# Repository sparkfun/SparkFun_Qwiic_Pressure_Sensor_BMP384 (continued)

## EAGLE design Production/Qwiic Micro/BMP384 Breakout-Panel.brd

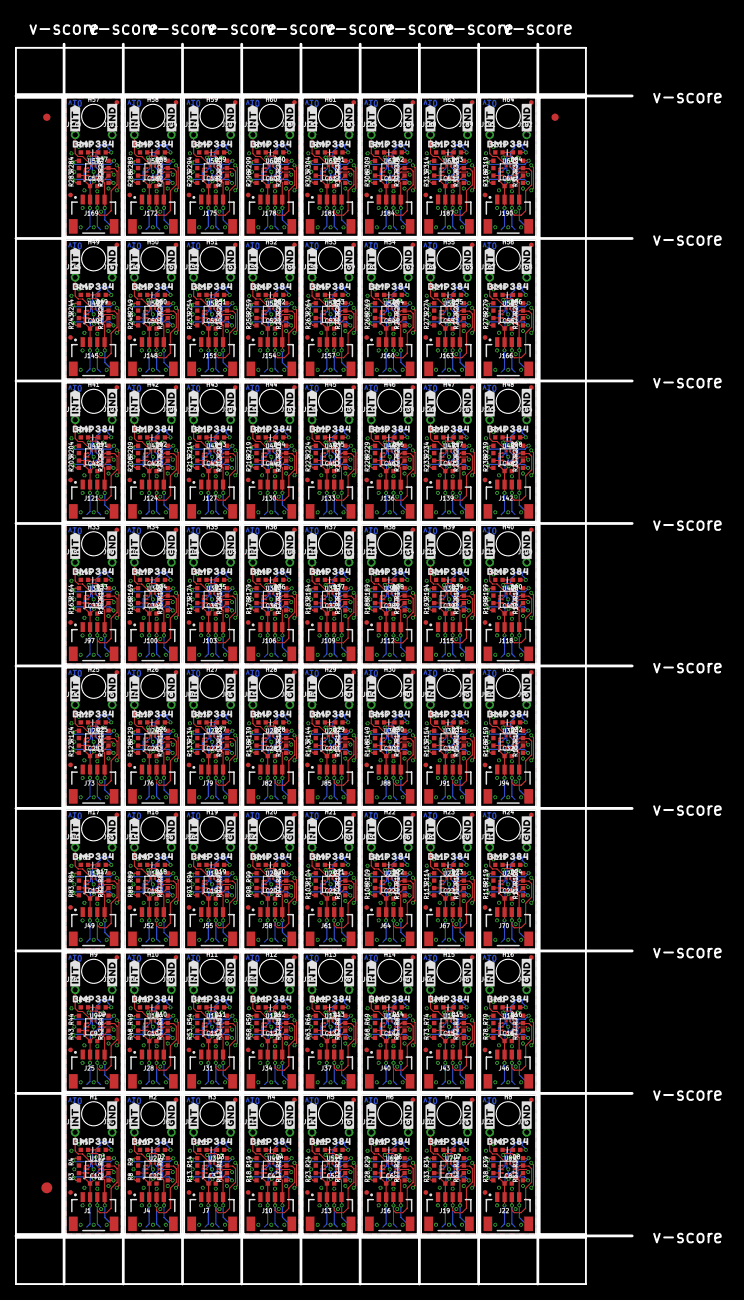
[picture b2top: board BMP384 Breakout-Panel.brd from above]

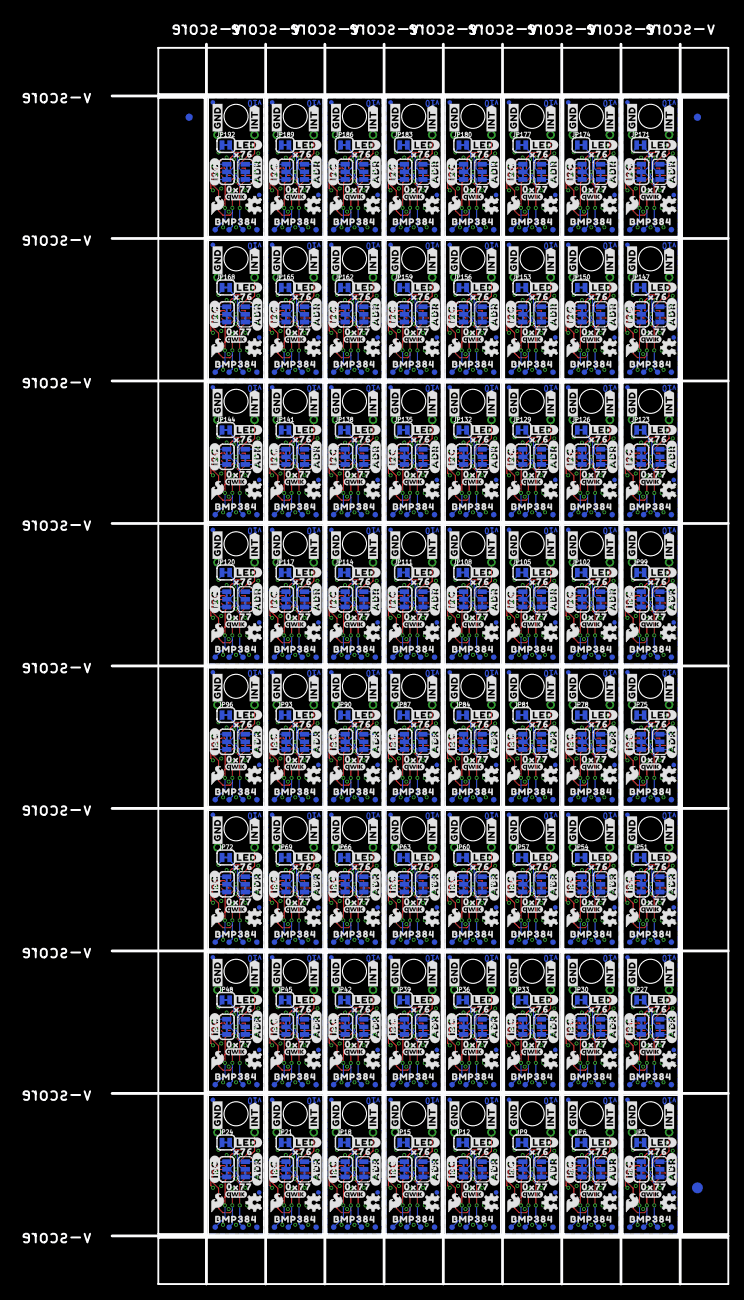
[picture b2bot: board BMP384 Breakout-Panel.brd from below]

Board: 4 copper layers, 84.6 x 170.2 mm, 2502 parts (1283 on the bottom side), 768 nets.

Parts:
C1, C2, C3, C4, C5, C6, C7, C8, C9, C10, C11, C12, C13, C14, C15, C16, C17, C18, C19, C20, C21, C22, C23, C24, C25, C26, C27, C28, C29, C30, C31, C32, C33, C34, C35, C36, C37, C38, C39, C40, C41, C42, C43, C44, C45, C46, C47, C48, C49, C50, C51, C52, C53, C54, C55, C56, C57, C58, C59, C60, C61, C62, C63, C64: 0.1uF; 0402-TIGHT
D1, D2, D3, D4, D5, D6, D7, D8, D9, D10, D11, D12, D13, D14, D15, D16, D17, D18, D19, D20, D21, D22, D23, D24, D25, D26, D27, D28, D29, D30, D31, D32, D33, D34, D35, D36, D37, D38, D39, D40, D41, D42, D43, D44, D45, D46, D47, D48, D49, D50, D51, D52, D53, D54, D55, D56, D57, D58, D59, D60, D61, D62, D63, D64: RED; LED-0402
E$1, E$2, E$3, E$4: FIDUCIAL-1X2
E$5, E$6: FIDUCIAL-1.5X3
FD1, FD2, FD3, FD4, FD5, FD6, FD7, FD8, FD9, FD10, FD11, FD12, FD13, FD14, FD15, FD16, FD17, FD18, FD19, FD20, FD21, FD22, FD23, FD24, FD25, FD26, FD27, FD28, FD29, FD30, FD31, FD32, FD33, FD34, FD35, FD36, FD37, FD38, FD39, FD40, FD41, FD42, FD43, FD44, FD45, FD46, FD47, FD48, FD49, FD50, FD51, FD52, FD53, FD54, FD55, FD56, FD57, FD58, FD59, FD60, FD61, FD62, FD63, FD64, FD65, FD66, FD67, FD68, FD69, FD70, FD71, FD72, FD73, FD74, FD75, FD76, FD77, FD78, FD79, FD80, FD81, FD82, FD83, FD84, FD85, FD86, FD87, FD88, FD89, FD90, FD91, FD92, FD93, FD94, FD95, FD96, FD97, FD98, FD99, FD100, FD101, FD102, FD103, FD104, FD105, FD106, FD107, FD108, FD109, FD110, FD111, FD112, FD113, FD114, FD115, FD116, FD117, FD118, FD119, FD120, FD121, FD122, FD123, FD124, FD125, FD126, FD127, FD128, FD129, FD130, FD131, FD132, FD133, FD134, FD135, FD136, FD137, FD138, FD139, FD140, FD141, FD142, FD143, FD144, FD145, FD146, FD147, FD148, FD149, FD150, FD151, FD152, FD153, FD154, FD155, FD156, FD157, FD158, FD159, FD160, FD161, FD162, FD163, FD164, FD165, FD166, FD167, FD168, FD169, FD170, FD171, FD172, FD173, FD174, FD175, FD176, FD177, FD178, FD179, FD180, FD181, FD182, FD183, FD184, FD185, FD186, FD187, FD188, FD189, FD190, FD191, FD192, FD193, FD194, FD195, FD196, FD197, FD198, FD199, FD200, FD201, FD202, FD203, FD204, FD205, FD206, FD207, FD208, FD209, FD210, FD211, FD212, FD213, FD214, FD215, FD216, FD217, FD218, FD219, FD220, FD221, FD222, FD223, FD224, FD225, FD226, FD227, FD228, FD229, FD230, FD231, FD232, FD233, FD234, FD235, FD236, FD237, FD238, FD239, FD240, FD241, FD242, FD243, FD244, FD245, FD246, FD247, FD248, FD249, FD250, FD251, FD252, FD253, FD254, FD255, FD256: FIDUCIALUFIDUCIAL; FIDUCIAL-MICRO
FRAME1, FRAME2, FRAME3, FRAME4, FRAME5, FRAME6, FRAME7, FRAME8, FRAME9, FRAME10, FRAME11, FRAME12, FRAME13, FRAME14, FRAME15, FRAME16, FRAME17, FRAME18, FRAME19, FRAME20, FRAME21, FRAME22, FRAME23, FRAME24, FRAME25, FRAME26, FRAME27, FRAME28, FRAME29, FRAME30, FRAME31, FRAME32, FRAME33, FRAME34, FRAME35, FRAME36, FRAME37, FRAME38, FRAME39, FRAME40, FRAME41, FRAME42, FRAME43, FRAME44, FRAME45, FRAME46, FRAME47, FRAME48, FRAME49, FRAME50, FRAME51, FRAME52, FRAME53, FRAME54, FRAME55, FRAME56, FRAME57, FRAME58, FRAME59, FRAME60, FRAME61, FRAME62, FRAME63, FRAME64: FRAME-LETTER; CREATIVE_COMMONS
H1, H2, H3, H4, H5, H6, H7, H8, H9, H10, H11, H12, H13, H14, H15, H16, H17, H18, H19, H20, H21, H22, H23, H24, H25, H26, H27, H28, H29, H30, H31, H32, H33, H34, H35, H36, H37, H38, H39, H40, H41, H42, H43, H44, H45, H46, H47, H48, H49, H50, H51, H52, H53, H54, H55, H56, H57, H58, H59, H60, H61, H62, H63, H64: STAND-OFF
J1, J4, J7, J10, J13, J16, J19, J22, J25, J28, J31, J34, J37, J40, J43, J46, J49, J52, J55, J58, J61, J64, J67, J70, J73, J76, J79, J82, J85, J88, J91, J94, J97, J100, J103, J106, J109, J112, J115, J118, J121, J124, J127, J130, J133, J136, J139, J142, J145, J148, J151, J154, J157, J160, J163, J166, J169, J172, J175, J178, J181, J184, J187, J190: QWIIC_RIGHT_ANGLE; JST04_1MM_RA
J2, J3, J5, J6, J8, J9, J11, J12, J14, J15, J17, J18, J20, J21, J23, J24, J26, J27, J29, J30, J32, J33, J35, J36, J38, J39, J41, J42, J44, J45, J47, J48, J50, J51, J53, J54, J56, J57, J59, J60, J62, J63, J65, J66, J68, J69, J71, J72, J74, J75, J77, J78, J80, J81, J83, J84, J86, J87, J89, J90, J92, J93, J95, J96, J98, J99, J101, J102, J104, J105, J107, J108, J110, J111, J113, J114, J116, J117, J119, J120, J122, J123, J125, J126, J128, J129, J131, J132, J134, J135, J137, J138, J140, J141, J143, J144, J146, J147, J149, J150, J152, J153, J155, J156, J158, J159, J161, J162, J164, J165, J167, J168, J170, J171, J173, J174, J176, J177, J179, J180, J182, J183, J185, J186, J188, J189, J191, J192: 1X01_1MM_NO_SILK
JP1, JP4, JP7, JP10, JP13, JP16, JP19, JP22, JP25, JP28, JP31, JP34, JP37, JP40, JP43, JP46, JP49, JP52, JP55, JP58, JP61, JP64, JP67, JP70, JP73, JP76, JP79, JP82, JP85, JP88, JP91, JP94, JP97, JP100, JP103, JP106, JP109, JP112, JP115, JP118, JP121, JP124, JP127, JP130, JP133, JP136, JP139, JP142, JP145, JP148, JP151, JP154, JP157, JP160, JP163, JP166, JP169, JP172, JP175, JP178, JP181, JP184, JP187, JP190: ADR; SMT-JUMPER_3_1-NC_TRACE_SILK
JP2, JP5, JP8, JP11, JP14, JP17, JP20, JP23, JP26, JP29, JP32, JP35, JP38, JP41, JP44, JP47, JP50, JP53, JP56, JP59, JP62, JP65, JP68, JP71, JP74, JP77, JP80, JP83, JP86, JP89, JP92, JP95, JP98, JP101, JP104, JP107, JP110, JP113, JP116, JP119, JP122, JP125, JP128, JP131, JP134, JP137, JP140, JP143, JP146, JP149, JP152, JP155, JP158, JP161, JP164, JP167, JP170, JP173, JP176, JP179, JP182, JP185, JP188, JP191: I2C; SMT-JUMPER_3_2-NC_TRACE_SILK
JP3, JP6, JP9, JP12, JP15, JP18, JP21, JP24, JP27, JP30, JP33, JP36, JP39, JP42, JP45, JP48, JP51, JP54, JP57, JP60, JP63, JP66, JP69, JP72, JP75, JP78, JP81, JP84, JP87, JP90, JP93, JP96, JP99, JP102, JP105, JP108, JP111, JP114, JP117, JP120, JP123, JP126, JP129, JP132, JP135, JP138, JP141, JP144, JP147, JP150, JP153, JP156, JP159, JP162, JP165, JP168, JP171, JP174, JP177, JP180, JP183, JP186, JP189, JP192: LED; SMT-JUMPER_2_NC_TRACE_SILK
LOGO1, LOGO5, LOGO9, LOGO13, LOGO17, LOGO21, LOGO25, LOGO29, LOGO33, LOGO37, LOGO41, LOGO45, LOGO49, LOGO53, LOGO57, LOGO61, LOGO65, LOGO69, LOGO73, LOGO77, LOGO81, LOGO85, LOGO89, LOGO93, LOGO97, LOGO101, LOGO105, LOGO109, LOGO113, LOGO117, LOGO121, LOGO125, LOGO129, LOGO133, LOGO137, LOGO141, LOGO145, LOGO149, LOGO153, LOGO157, LOGO161, LOGO165, LOGO169, LOGO173, LOGO177, LOGO181, LOGO185, LOGO189, LOGO193, LOGO197, LOGO201, LOGO205, LOGO209, LOGO213, LOGO217, LOGO221, LOGO225, LOGO229, LOGO233, LOGO237, LOGO241, LOGO245, LOGO249, LOGO253: SFE_LOGO_FLAME.1_INCH; SFE_LOGO_FLAME_.1
LOGO2, LOGO6, LOGO10, LOGO14, LOGO18, LOGO22, LOGO26, LOGO30, LOGO34, LOGO38, LOGO42, LOGO46, LOGO50, LOGO54, LOGO58, LOGO62, LOGO66, LOGO70, LOGO74, LOGO78, LOGO82, LOGO86, LOGO90, LOGO94, LOGO98, LOGO102, LOGO106, LOGO110, LOGO114, LOGO118, LOGO122, LOGO126, LOGO130, LOGO134, LOGO138, LOGO142, LOGO146, LOGO150, LOGO154, LOGO158, LOGO162, LOGO166, LOGO170, LOGO174, LOGO178, LOGO182, LOGO186, LOGO190, LOGO194, LOGO198, LOGO202, LOGO206, LOGO210, LOGO214, LOGO218, LOGO222, LOGO226, LOGO230, LOGO234, LOGO238, LOGO242, LOGO246, LOGO250, LOGO254: QWIIC_LOGO_3MM; QWIIC_3MM
LOGO3, LOGO7, LOGO11, LOGO15, LOGO19, LOGO23, LOGO27, LOGO31, LOGO35, LOGO39, LOGO43, LOGO47, LOGO51, LOGO55, LOGO59, LOGO63, LOGO67, LOGO71, LOGO75, LOGO79, LOGO83, LOGO87, LOGO91, LOGO95, LOGO99, LOGO103, LOGO107, LOGO111, LOGO115, LOGO119, LOGO123, LOGO127, LOGO131, LOGO135, LOGO139, LOGO143, LOGO147, LOGO151, LOGO155, LOGO159, LOGO163, LOGO167, LOGO171, LOGO175, LOGO179, LOGO183, LOGO187, LOGO191, LOGO195, LOGO199, LOGO203, LOGO207, LOGO211, LOGO215, LOGO219, LOGO223, LOGO227, LOGO231, LOGO235, LOGO239, LOGO243, LOGO247, LOGO251, LOGO255: OSHW-LOGOMINI; OSHW-LOGO-MINI
LOGO4, LOGO8, LOGO12, LOGO16, LOGO20, LOGO24, LOGO28, LOGO32, LOGO36, LOGO40, LOGO44, LOGO48, LOGO52, LOGO56, LOGO60, LOGO64, LOGO68, LOGO72, LOGO76, LOGO80, LOGO84, LOGO88, LOGO92, LOGO96, LOGO100, LOGO104, LOGO108, LOGO112, LOGO116, LOGO120, LOGO124, LOGO128, LOGO132, LOGO136, LOGO140, LOGO144, LOGO148, LOGO152, LOGO156, LOGO160, LOGO164, LOGO168, LOGO172, LOGO176, LOGO180, LOGO184, LOGO188, LOGO192, LOGO196, LOGO200, LOGO204, LOGO208, LOGO212, LOGO216, LOGO220, LOGO224, LOGO228, LOGO232, LOGO236, LOGO240, LOGO244, LOGO248, LOGO252, LOGO256: SFE_LOGO_NAMEBLANK; BLANK
R1, R2, R6, R7, R11, R12, R16, R17, R21, R22, R26, R27, R31, R32, R36, R37, R41, R42, R46, R47, R51, R52, R56, R57, R61, R62, R66, R67, R71, R72, R76, R77, R81, R82, R86, R87, R91, R92, R96, R97, R101, R102, R106, R107, R111, R112, R116, R117, R121, R122, R126, R127, R131, R132, R136, R137, R141, R142, R146, R147, R151, R152, R156, R157, R161, R162, R166, R167, R171, R172, R176, R177, R181, R182, R186, R187, R191, R192, R196, R197, R201, R202, R206, R207, R211, R212, R216, R217, R221, R222, R226, R227, R231, R232, R236, R237, R241, R242, R246, R247, R251, R252, R256, R257, R261, R262, R266, R267, R271, R272, R276, R277, R281, R282, R286, R287, R291, R292, R296, R297, R301, R302, R306, R307, R311, R312, R316, R317: 2.2k; 0402-TIGHT
R3, R4, R8, R9, R13, R14, R18, R19, R23, R24, R28, R29, R33, R34, R38, R39, R43, R44, R48, R49, R53, R54, R58, R59, R63, R64, R68, R69, R73, R74, R78, R79, R83, R84, R88, R89, R93, R94, R98, R99, R103, R104, R108, R109, R113, R114, R118, R119, R123, R124, R128, R129, R133, R134, R138, R139, R143, R144, R148, R149, R153, R154, R158, R159, R163, R164, R168, R169, R173, R174, R178, R179, R183, R184, R188, R189, R193, R194, R198, R199, R203, R204, R208, R209, R213, R214, R218, R219, R223, R224, R228, R229, R233, R234, R238, R239, R243, R244, R248, R249, R253, R254, R258, R259, R263, R264, R268, R269, R273, R274, R278, R279, R283, R284, R288, R289, R293, R294, R298, R299, R303, R304, R308, R309, R313, R314, R318, R319: 10K; 0402-TIGHT
R5, R10, R15, R20, R25, R30, R35, R40, R45, R50, R55, R60, R65, R70, R75, R80, R85, R90, R95, R100, R105, R110, R115, R120, R125, R130, R135, R140, R145, R150, R155, R160, R165, R170, R175, R180, R185, R190, R195, R200, R205, R210, R215, R220, R225, R230, R235, R240, R245, R250, R255, R260, R265, R270, R275, R280, R285, R290, R295, R300, R305, R310, R315, R320: 1k; 0402-TIGHT
TP1, TP2, TP3, TP4, TP5, TP6, TP7, TP8, TP9, TP10, TP11, TP12, TP13, TP14, TP15, TP16, TP17, TP18, TP19, TP20, TP21, TP22, TP23, TP24, TP25, TP26, TP27, TP28, TP29, TP30, TP31, TP32, TP33, TP34, TP35, TP36, TP37, TP38, TP39, TP40, TP41, TP42, TP43, TP44, TP45, TP46, TP47, TP48, TP49, TP50, TP51, TP52, TP53, TP54, TP55, TP56, TP57, TP58, TP59, TP60, TP61, TP62, TP63, TP64, TP65, TP66, TP67, TP68, TP69, TP70, TP71, TP72, TP73, TP74, TP75, TP76, TP77, TP78, TP79, TP80, TP81, TP82, TP83, TP84, TP85, TP86, TP87, TP88, TP89, TP90, TP91, TP92, TP93, TP94, TP95, TP96, TP97, TP98, TP99, TP100, TP101, TP102, TP103, TP104, TP105, TP106, TP107, TP108, TP109, TP110, TP111, TP112, TP113, TP114, TP115, TP116, TP117, TP118, TP119, TP120, TP121, TP122, TP123, TP124, TP125, TP126, TP127, TP128, TP129, TP130, TP131, TP132, TP133, TP134, TP135, TP136, TP137, TP138, TP139, TP140, TP141, TP142, TP143, TP144, TP145, TP146, TP147, TP148, TP149, TP150, TP151, TP152, TP153, TP154, TP155, TP156, TP157, TP158, TP159, TP160, TP161, TP162, TP163, TP164, TP165, TP166, TP167, TP168, TP169, TP170, TP171, TP172, TP173, TP174, TP175, TP176, TP177, TP178, TP179, TP180, TP181, TP182, TP183, TP184, TP185, TP186, TP187, TP188, TP189, TP190, TP191, TP192, TP193, TP194, TP195, TP196, TP197, TP198, TP199, TP200, TP201, TP202, TP203, TP204, TP205, TP206, TP207, TP208, TP209, TP210, TP211, TP212, TP213, TP214, TP215, TP216, TP217, TP218, TP219, TP220, TP221, TP222, TP223, TP224, TP225, TP226, TP227, TP228, TP229, TP230, TP231, TP232, TP233, TP234, TP235, TP236, TP237, TP238, TP239, TP240, TP241, TP242, TP243, TP244, TP245, TP246, TP247, TP248, TP249, TP250, TP251, TP252, TP253, TP254, TP255, TP256: TEST-POINT3; PAD.03X.03
U1, U2, U3, U4, U5, U6, U7, U8, U9, U10, U11, U12, U13, U14, U15, U16, U17, U18, U19, U20, U21, U22, U23, U24, U25, U26, U27, U28, U29, U30, U31, U32, U33, U34, U35, U36, U37, U38, U39, U40, U41, U42, U43, U44, U45, U46, U47, U48, U49, U50, U51, U52, U53, U54, U55, U56, U57, U58, U59, U60, U61, U62, U63, U64: BMP384; LGA-10
U$1, U$10, U$23, U$34, U$45, U$56, U$67, U$78, U$89, U$100, U$111, U$122, U$133, U$144, U$155, U$166, U$177, U$188, U$199, U$210, U$221, U$232, U$243, U$254, U$265, U$276, U$287, U$298, U$309, U$320, U$331, U$342, U$353, U$364, U$375, U$386, U$397, U$408, U$419, U$430, U$441, U$452, U$463, U$474, U$485, U$496, U$507, U$518, U$529, U$540, U$551, U$562, U$573, U$584, U$595, U$606, U$617, U$628, U$639, U$650, U$661, U$672, U$683, U$694: #I2C#0
U$2, U$13, U$24, U$35, U$46, U$57, U$68, U$79, U$90, U$101, U$112, U$123, U$134, U$145, U$156, U$167, U$178, U$189, U$200, U$211, U$222, U$233, U$244, U$255, U$266, U$277, U$288, U$299, U$310, U$321, U$332, U$343, U$354, U$365, U$376, U$387, U$398, U$409, U$420, U$431, U$442, U$453, U$464, U$475, U$486, U$497, U$508, U$519, U$530, U$541, U$552, U$563, U$574, U$585, U$596, U$607, U$618, U$629, U$640, U$651, U$662, U$673, U$684, U$695: #ADR#0
U$3, U$19, U$30, U$41, U$52, U$63, U$74, U$85, U$96, U$107, U$118, U$129, U$140, U$151, U$162, U$173, U$184, U$195, U$206, U$217, U$228, U$239, U$250, U$261, U$272, U$283, U$294, U$305, U$316, U$327, U$338, U$349, U$360, U$371, U$382, U$393, U$404, U$415, U$426, U$437, U$448, U$459, U$470, U$481, U$492, U$503, U$514, U$525, U$536, U$547, U$558, U$569, U$580, U$591, U$602, U$613, U$624, U$635, U$646, U$657, U$668, U$679, U$690, U$701: #LED#0
U$4, U$11, U$18, U$20, U$29, U$31, U$40, U$42, U$51, U$53, U$62, U$64, U$73, U$75, U$84, U$86, U$95, U$97, U$106, U$108, U$117, U$119, U$128, U$130, U$139, U$141, U$150, U$152, U$161, U$163, U$172, U$174, U$183, U$185, U$194, U$196, U$205, U$207, U$216, U$218, U$227, U$229, U$238, U$240, U$249, U$251, U$260, U$262, U$271, U$273, U$282, U$284, U$293, U$295, U$304, U$306, U$315, U$317, U$326, U$328, U$337, U$339, U$348, U$350, U$359, U$361, U$370, U$372, U$381, U$383, U$392, U$394, U$403, U$405, U$414, U$416, U$425, U$427, U$436, U$438, U$447, U$449, U$458, U$460, U$469, U$471, U$480, U$482, U$491, U$493, U$502, U$504, U$513, U$515, U$524, U$526, U$535, U$537, U$546, U$548, U$557, U$559, U$568, U$570, U$579, U$581, U$590, U$592, U$601, U$603, U$612, U$614, U$623, U$625, U$634, U$636, U$645, U$647, U$656, U$658, U$667, U$669, U$678, U$680, U$689, U$691, U$700, U$702: BMP3840
U$5, U$6, U$14, U$15, U$25, U$26, U$36, U$37, U$47, U$48, U$58, U$59, U$69, U$70, U$80, U$81, U$91, U$92, U$102, U$103, U$113, U$114, U$124, U$125, U$135, U$136, U$146, U$147, U$157, U$158, U$168, U$169, U$179, U$180, U$190, U$191, U$201, U$202, U$212, U$213, U$223, U$224, U$234, U$235, U$245, U$246, U$256, U$257, U$267, U$268, U$278, U$279, U$289, U$290, U$300, U$301, U$311, U$312, U$322, U$323, U$333, U$334, U$344, U$345, U$355, U$356, U$366, U$367, U$377, U$378, U$388, U$389, U$399, U$400, U$410, U$411, U$421, U$422, U$432, U$433, U$443, U$444, U$454, U$455, U$465, U$466, U$476, U$477, U$487, U$488, U$498, U$499, U$509, U$510, U$520, U$521, U$531, U$532, U$542, U$543, U$553, U$554, U$564, U$565, U$575, U$576, U$586, U$587, U$597, U$598, U$608, U$609, U$619, U$620, U$630, U$631, U$641, U$642, U$652, U$653, U$663, U$664, U$674, U$675, U$685, U$686, U$696, U$697: #GND#0
U$7, U$8, U$16, U$17, U$27, U$28, U$38, U$39, U$49, U$50, U$60, U$61, U$71, U$72, U$82, U$83, U$93, U$94, U$104, U$105, U$115, U$116, U$126, U$127, U$137, U$138, U$148, U$149, U$159, U$160, U$170, U$171, U$181, U$182, U$192, U$193, U$203, U$204, U$214, U$215, U$225, U$226, U$236, U$237, U$247, U$248, U$258, U$259, U$269, U$270, U$280, U$281, U$291, U$292, U$302, U$303, U$313, U$314, U$324, U$325, U$335, U$336, U$346, U$347, U$357, U$358, U$368, U$369, U$379, U$380, U$390, U$391, U$401, U$402, U$412, U$413, U$423, U$424, U$434, U$435, U$445, U$446, U$456, U$457, U$467, U$468, U$478, U$479, U$489, U$490, U$500, U$501, U$511, U$512, U$522, U$523, U$533, U$534, U$544, U$545, U$555, U$556, U$566, U$567, U$577, U$578, U$588, U$589, U$599, U$600, U$610, U$611, U$621, U$622, U$632, U$633, U$643, U$644, U$654, U$655, U$665, U$666, U$676, U$677, U$687, U$688, U$698, U$699: #INT#0
U$9, U$22, U$33, U$44, U$55, U$66, U$77, U$88, U$99, U$110, U$121, U$132, U$143, U$154, U$165, U$176, U$187, U$198, U$209, U$220, U$231, U$242, U$253, U$264, U$275, U$286, U$297, U$308, U$319, U$330, U$341, U$352, U$363, U$374, U$385, U$396, U$407, U$418, U$429, U$440, U$451, U$462, U$473, U$484, U$495, U$506, U$517, U$528, U$539, U$550, U$561, U$572, U$583, U$594, U$605, U$616, U$627, U$638, U$649, U$660, U$671, U$682, U$693, U$704: X760
U$12, U$21, U$32, U$43, U$54, U$65, U$76, U$87, U$98, U$109, U$120, U$131, U$142, U$153, U$164, U$175, U$186, U$197, U$208, U$219, U$230, U$241, U$252, U$263, U$274, U$285, U$296, U$307, U$318, U$329, U$340, U$351, U$362, U$373, U$384, U$395, U$406, U$417, U$428, U$439, U$450, U$461, U$472, U$483, U$494, U$505, U$516, U$527, U$538, U$549, U$560, U$571, U$582, U$593, U$604, U$615, U$626, U$637, U$648, U$659, U$670, U$681, U$692, U$703: 0X770

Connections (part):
GND: C1.2, J1.1, J3.1, R4.1, R5.1, TP1.1, U1.3, U1.8, U1.9
GND1: C2.2, J4.1, J6.1, R9.1, R10.1, TP5.1, U2.3, U2.8, U2.9
GND2: C3.2, J7.1, J9.1, R14.1, R15.1, TP9.1, U3.3, U3.8, U3.9
GND3: C4.2, J10.1, J12.1, R19.1, R20.1, TP13.1, U4.3, U4.8, U4.9
GND4: C5.2, J13.1, J15.1, R24.1, R25.1, TP17.1, U5.3, U5.8, U5.9
GND5: C6.2, J16.1, J18.1, R29.1, R30.1, TP21.1, U6.3, U6.8, U6.9
GND6: C7.2, J19.1, J21.1, R34.1, R35.1, TP25.1, U7.3, U7.8, U7.9
GND7: C8.2, J22.1, J24.1, R39.1, R40.1, TP29.1, U8.3, U8.8, U8.9
GND8: C9.2, J25.1, J27.1, R44.1, R45.1, TP33.1, U9.3, U9.8, U9.9
GND9: C10.2, J28.1, J30.1, R49.1, R50.1, TP37.1, U10.3, U10.8, U10.9
GND10: C11.2, J31.1, J33.1, R54.1, R55.1, TP41.1, U11.3, U11.8, U11.9
GND11: C12.2, J34.1, J36.1, R59.1, R60.1, TP45.1, U12.3, U12.8, U12.9
GND12: C13.2, J37.1, J39.1, R64.1, R65.1, TP49.1, U13.3, U13.8, U13.9
GND13: C14.2, J40.1, J42.1, R69.1, R70.1, TP53.1, U14.3, U14.8, U14.9
GND14: C15.2, J43.1, J45.1, R74.1, R75.1, TP57.1, U15.3, U15.8, U15.9
GND15: C16.2, J46.1, J48.1, R79.1, R80.1, TP61.1, U16.3, U16.8, U16.9
GND16: C17.2, J49.1, J51.1, R84.1, R85.1, TP65.1, U17.3, U17.8, U17.9
GND17: C18.2, J52.1, J54.1, R89.1, R90.1, TP69.1, U18.3, U18.8, U18.9
GND18: C19.2, J55.1, J57.1, R94.1, R95.1, TP73.1, U19.3, U19.8, U19.9
GND19: C20.2, J58.1, J60.1, R99.1, R100.1, TP77.1, U20.3, U20.8, U20.9
GND20: C21.2, J61.1, J63.1, R104.1, R105.1, TP81.1, U21.3, U21.8, U21.9
GND21: C22.2, J64.1, J66.1, R109.1, R110.1, TP85.1, U22.3, U22.8, U22.9
GND22: C23.2, J67.1, J69.1, R114.1, R115.1, TP89.1, U23.3, U23.8, U23.9
GND23: C24.2, J70.1, J72.1, R119.1, R120.1, TP93.1, U24.3, U24.8, U24.9
GND24: C25.2, J73.1, J75.1, R124.1, R125.1, TP97.1, U25.3, U25.8, U25.9
GND25: C26.2, J76.1, J78.1, R129.1, R130.1, TP101.1, U26.3, U26.8, U26.9
GND26: C27.2, J79.1, J81.1, R134.1, R135.1, TP105.1, U27.3, U27.8, U27.9
GND27: C28.2, J82.1, J84.1, R139.1, R140.1, TP109.1, U28.3, U28.8, U28.9
GND28: C29.2, J85.1, J87.1, R144.1, R145.1, TP113.1, U29.3, U29.8, U29.9
GND29: C30.2, J88.1, J90.1, R149.1, R150.1, TP117.1, U30.3, U30.8, U30.9
GND30: C31.2, J91.1, J93.1, R154.1, R155.1, TP121.1, U31.3, U31.8, U31.9
GND31: C32.2, J94.1, J96.1, R159.1, R160.1, TP125.1, U32.3, U32.8, U32.9
GND32: C33.2, J97.1, J99.1, R164.1, R165.1, TP129.1, U33.3, U33.8, U33.9
GND33: C34.2, J100.1, J102.1, R169.1, R170.1, TP133.1, U34.3, U34.8, U34.9
GND34: C35.2, J103.1, J105.1, R174.1, R175.1, TP137.1, U35.3, U35.8, U35.9
GND35: C36.2, J106.1, J108.1, R179.1, R180.1, TP141.1, U36.3, U36.8, U36.9
GND36: C37.2, J109.1, J111.1, R184.1, R185.1, TP145.1, U37.3, U37.8, U37.9
GND37: C38.2, J112.1, J114.1, R189.1, R190.1, TP149.1, U38.3, U38.8, U38.9
GND38: C39.2, J115.1, J117.1, R194.1, R195.1, TP153.1, U39.3, U39.8, U39.9
GND39: C40.2, J118.1, J120.1, R199.1, R200.1, TP157.1, U40.3, U40.8, U40.9
GND40: C41.2, J121.1, J123.1, R204.1, R205.1, TP161.1, U41.3, U41.8, U41.9
GND41: C42.2, J124.1, J126.1, R209.1, R210.1, TP165.1, U42.3, U42.8, U42.9
GND42: C43.2, J127.1, J129.1, R214.1, R215.1, TP169.1, U43.3, U43.8, U43.9
GND43: C44.2, J130.1, J132.1, R219.1, R220.1, TP173.1, U44.3, U44.8, U44.9
GND44: C45.2, J133.1, J135.1, R224.1, R225.1, TP177.1, U45.3, U45.8, U45.9
GND45: C46.2, J136.1, J138.1, R229.1, R230.1, TP181.1, U46.3, U46.8, U46.9
GND46: C47.2, J139.1, J141.1, R234.1, R235.1, TP185.1, U47.3, U47.8, U47.9
GND47: C48.2, J142.1, J144.1, R239.1, R240.1, TP189.1, U48.3, U48.8, U48.9
GND48: C49.2, J145.1, J147.1, R244.1, R245.1, TP193.1, U49.3, U49.8, U49.9
GND49: C50.2, J148.1, J150.1, R249.1, R250.1, TP197.1, U50.3, U50.8, U50.9
GND50: C51.2, J151.1, J153.1, R254.1, R255.1, TP201.1, U51.3, U51.8, U51.9
GND51: C52.2, J154.1, J156.1, R259.1, R260.1, TP205.1, U52.3, U52.8, U52.9
GND52: C53.2, J157.1, J159.1, R264.1, R265.1, TP209.1, U53.3, U53.8, U53.9
GND53: C54.2, J160.1, J162.1, R269.1, R270.1, TP213.1, U54.3, U54.8, U54.9
GND54: C55.2, J163.1, J165.1, R274.1, R275.1, TP217.1, U55.3, U55.8, U55.9
GND55: C56.2, J166.1, J168.1, R279.1, R280.1, TP221.1, U56.3, U56.8, U56.9
GND56: C57.2, J169.1, J171.1, R284.1, R285.1, TP225.1, U57.3, U57.8, U57.9
GND57: C58.2, J172.1, J174.1, R289.1, R290.1, TP229.1, U58.3, U58.8, U58.9
GND58: C59.2, J175.1, J177.1, R294.1, R295.1, TP233.1, U59.3, U59.8, U59.9
GND59: C60.2, J178.1, J180.1, R299.1, R300.1, TP237.1, U60.3, U60.8, U60.9
GND60: C61.2, J181.1, J183.1, R304.1, R305.1, TP241.1, U61.3, U61.8, U61.9
GND61: C62.2, J184.1, J186.1, R309.1, R310.1, TP245.1, U62.3, U62.8, U62.9
GND62: C63.2, J187.1, J189.1, R314.1, R315.1, TP249.1, U63.3, U63.8, U63.9
GND63: C64.2, J190.1, J192.1, R319.1, R320.1, TP253.1, U64.3, U64.8, U64.9
INT: J2.1, U1.7
INT1: J5.1, U2.7
INT2: J8.1, U3.7
INT3: J11.1, U4.7
INT4: J14.1, U5.7
INT5: J17.1, U6.7
INT6: J20.1, U7.7
INT7: J23.1, U8.7
INT8: J26.1, U9.7
INT9: J29.1, U10.7
INT10: J32.1, U11.7
INT11: J35.1, U12.7
INT12: J38.1, U13.7
INT13: J41.1, U14.7
INT14: J44.1, U15.7
INT15: J47.1, U16.7
INT16: J50.1, U17.7
INT17: J53.1, U18.7
INT18: J56.1, U19.7
INT19: J59.1, U20.7
INT20: J62.1, U21.7
INT21: J65.1, U22.7
INT22: J68.1, U23.7
INT23: J71.1, U24.7
INT24: J74.1, U25.7
INT25: J77.1, U26.7
INT26: J80.1, U27.7
INT27: J83.1, U28.7
INT28: J86.1, U29.7
INT29: J89.1, U30.7
INT30: J92.1, U31.7
INT31: J95.1, U32.7
INT32: J98.1, U33.7
INT33: J101.1, U34.7
INT34: J104.1, U35.7
INT35: J107.1, U36.7
INT36: J110.1, U37.7
INT37: J113.1, U38.7
INT38: J116.1, U39.7
INT39: J119.1, U40.7
INT40: J122.1, U41.7
INT41: J125.1, U42.7
INT42: J128.1, U43.7
INT43: J131.1, U44.7
INT44: J134.1, U45.7
INT45: J137.1, U46.7
INT46: J140.1, U47.7
INT47: J143.1, U48.7
INT48: J146.1, U49.7
INT49: J149.1, U50.7
INT50: J152.1, U51.7
INT51: J155.1, U52.7
INT52: J158.1, U53.7
INT53: J161.1, U54.7
INT54: J164.1, U55.7
INT55: J167.1, U56.7
INT56: J170.1, U57.7
INT57: J173.1, U58.7
INT58: J176.1, U59.7
INT59: J179.1, U60.7
INT60: J182.1, U61.7
INT61: J185.1, U62.7
INT62: J188.1, U63.7
INT63: J191.1, U64.7
unnamed: JP1.3, R3.1
unnamed: JP1.1, R4.2
unnamed: JP2.1, R2.1
unnamed: JP2.3, R1.2
unnamed: D1.A, JP3.1
unnamed: D1.C, R5.2
unnamed: JP4.3, R8.1
unnamed: JP4.1, R9.2
unnamed: JP5.1, R7.1
unnamed: JP5.3, R6.2
unnamed: D2.A, JP6.1
unnamed: D2.C, R10.2
unnamed: JP7.3, R13.1
unnamed: JP7.1, R14.2
unnamed: JP8.1, R12.1
unnamed: JP8.3, R11.2
unnamed: D3.A, JP9.1
unnamed: D3.C, R15.2
unnamed: JP10.3, R18.1
unnamed: JP10.1, R19.2
unnamed: JP11.1, R17.1
unnamed: JP11.3, R16.2
unnamed: D4.A, JP12.1
unnamed: D4.C, R20.2
unnamed: JP13.3, R23.1
unnamed: JP13.1, R24.2
unnamed: JP14.1, R22.1
unnamed: JP14.3, R21.2
unnamed: D5.A, JP15.1
unnamed: D5.C, R25.2
unnamed: JP16.3, R28.1
unnamed: JP16.1, R29.2
unnamed: JP17.1, R27.1
unnamed: JP17.3, R26.2
unnamed: D6.A, JP18.1
unnamed: D6.C, R30.2
unnamed: JP19.3, R33.1
unnamed: JP19.1, R34.2
unnamed: JP20.1, R32.1
unnamed: JP20.3, R31.2
unnamed: D7.A, JP21.1
unnamed: D7.C, R35.2
unnamed: JP22.3, R38.1
unnamed: JP22.1, R39.2
unnamed: JP23.1, R37.1
unnamed: JP23.3, R36.2
unnamed: D8.A, JP24.1
unnamed: D8.C, R40.2
unnamed: JP25.3, R43.1
unnamed: JP25.1, R44.2
unnamed: JP26.1, R42.1
unnamed: JP26.3, R41.2
unnamed: D9.A, JP27.1
unnamed: D9.C, R45.2
unnamed: JP28.3, R48.1
unnamed: JP28.1, R49.2
unnamed: JP29.1, R47.1
unnamed: JP29.3, R46.2
unnamed: D10.A, JP30.1
unnamed: D10.C, R50.2
unnamed: JP31.3, R53.1
unnamed: JP31.1, R54.2
unnamed: JP32.1, R52.1
unnamed: JP32.3, R51.2
unnamed: D11.A, JP33.1
unnamed: D11.C, R55.2
unnamed: JP34.3, R58.1
unnamed: JP34.1, R59.2
unnamed: JP35.1, R57.1
unnamed: JP35.3, R56.2
unnamed: D12.A, JP36.1
unnamed: D12.C, R60.2
unnamed: JP37.3, R63.1
unnamed: JP37.1, R64.2
unnamed: JP38.1, R62.1
unnamed: JP38.3, R61.2
unnamed: D13.A, JP39.1
unnamed: D13.C, R65.2
unnamed: JP40.3, R68.1
unnamed: JP40.1, R69.2
unnamed: JP41.1, R67.1
unnamed: JP41.3, R66.2
unnamed: D14.A, JP42.1
unnamed: D14.C, R70.2
unnamed: JP43.3, R73.1
unnamed: JP43.1, R74.2
unnamed: JP44.1, R72.1
unnamed: JP44.3, R71.2
unnamed: D15.A, JP45.1
unnamed: D15.C, R75.2
unnamed: JP46.3, R78.1
unnamed: JP46.1, R79.2
unnamed: JP47.1, R77.1
unnamed: JP47.3, R76.2
unnamed: D16.A, JP48.1
unnamed: D16.C, R80.2
unnamed: JP49.3, R83.1
unnamed: JP49.1, R84.2
unnamed: JP50.1, R82.1
unnamed: JP50.3, R81.2
unnamed: D17.A, JP51.1
unnamed: D17.C, R85.2
unnamed: JP52.3, R88.1
unnamed: JP52.1, R89.2
unnamed: JP53.1, R87.1
unnamed: JP53.3, R86.2
unnamed: D18.A, JP54.1
unnamed: D18.C, R90.2
unnamed: JP55.3, R93.1
unnamed: JP55.1, R94.2
unnamed: JP56.1, R92.1
unnamed: JP56.3, R91.2
unnamed: D19.A, JP57.1
unnamed: D19.C, R95.2
unnamed: JP58.3, R98.1
unnamed: JP58.1, R99.2
unnamed: JP59.1, R97.1
unnamed: JP59.3, R96.2
unnamed: D20.A, JP60.1
unnamed: D20.C, R100.2
unnamed: JP61.3, R103.1
unnamed: JP61.1, R104.2
unnamed: JP62.1, R102.1
unnamed: JP62.3, R101.2
unnamed: D21.A, JP63.1
unnamed: D21.C, R105.2
unnamed: JP64.3, R108.1
unnamed: JP64.1, R109.2
unnamed: JP65.1, R107.1
unnamed: JP65.3, R106.2
unnamed: D22.A, JP66.1
unnamed: D22.C, R110.2
unnamed: JP67.3, R113.1
unnamed: JP67.1, R114.2
unnamed: JP68.1, R112.1
unnamed: JP68.3, R111.2
unnamed: D23.A, JP69.1
unnamed: D23.C, R115.2
unnamed: JP70.3, R118.1
unnamed: JP70.1, R119.2
unnamed: JP71.1, R117.1
unnamed: JP71.3, R116.2
unnamed: D24.A, JP72.1
unnamed: D24.C, R120.2
unnamed: JP73.3, R123.1
unnamed: JP73.1, R124.2
unnamed: JP74.1, R122.1
unnamed: JP74.3, R121.2
unnamed: D25.A, JP75.1
unnamed: D25.C, R125.2
unnamed: JP76.3, R128.1
unnamed: JP76.1, R129.2
unnamed: JP77.1, R127.1
unnamed: JP77.3, R126.2
unnamed: D26.A, JP78.1
unnamed: D26.C, R130.2
unnamed: JP79.3, R133.1
unnamed: JP79.1, R134.2
unnamed: JP80.1, R132.1
unnamed: JP80.3, R131.2
unnamed: D27.A, JP81.1
unnamed: D27.C, R135.2
unnamed: JP82.3, R138.1
unnamed: JP82.1, R139.2
unnamed: JP83.1, R137.1
unnamed: JP83.3, R136.2
unnamed: D28.A, JP84.1
unnamed: D28.C, R140.2
unnamed: JP85.3, R143.1
unnamed: JP85.1, R144.2
unnamed: JP86.1, R142.1
unnamed: JP86.3, R141.2
unnamed: D29.A, JP87.1
unnamed: D29.C, R145.2
unnamed: JP88.3, R148.1
unnamed: JP88.1, R149.2
unnamed: JP89.1, R147.1
unnamed: JP89.3, R146.2
unnamed: D30.A, JP90.1
unnamed: D30.C, R150.2
unnamed: JP91.3, R153.1
unnamed: JP91.1, R154.2
unnamed: JP92.1, R152.1
unnamed: JP92.3, R151.2
unnamed: D31.A, JP93.1
unnamed: D31.C, R155.2
unnamed: JP94.3, R158.1
unnamed: JP94.1, R159.2
unnamed: JP95.1, R157.1
unnamed: JP95.3, R156.2
unnamed: D32.A, JP96.1
unnamed: D32.C, R160.2
unnamed: JP97.3, R163.1
unnamed: JP97.1, R164.2
unnamed: JP98.1, R162.1
unnamed: JP98.3, R161.2
unnamed: D33.A, JP99.1
unnamed: D33.C, R165.2
unnamed: JP100.3, R168.1
unnamed: JP100.1, R169.2
unnamed: JP101.1, R167.1
unnamed: JP101.3, R166.2
unnamed: D34.A, JP102.1
unnamed: D34.C, R170.2
unnamed: JP103.3, R173.1
unnamed: JP103.1, R174.2
unnamed: JP104.1, R172.1
unnamed: JP104.3, R171.2
unnamed: D35.A, JP105.1
unnamed: D35.C, R175.2
unnamed: JP106.3, R178.1
unnamed: JP106.1, R179.2
unnamed: JP107.1, R177.1
unnamed: JP107.3, R176.2
unnamed: D36.A, JP108.1
unnamed: D36.C, R180.2
unnamed: JP109.3, R183.1
unnamed: JP109.1, R184.2
unnamed: JP110.1, R182.1
unnamed: JP110.3, R181.2
unnamed: D37.A, JP111.1
unnamed: D37.C, R185.2
unnamed: JP112.3, R188.1
unnamed: JP112.1, R189.2
unnamed: JP113.1, R187.1
unnamed: JP113.3, R186.2
unnamed: D38.A, JP114.1
unnamed: D38.C, R190.2
unnamed: JP115.3, R193.1
unnamed: JP115.1, R194.2
unnamed: JP116.1, R192.1
unnamed: JP116.3, R191.2
unnamed: D39.A, JP117.1
unnamed: D39.C, R195.2
unnamed: JP118.3, R198.1
unnamed: JP118.1, R199.2
unnamed: JP119.1, R197.1
unnamed: JP119.3, R196.2
unnamed: D40.A, JP120.1
unnamed: D40.C, R200.2
unnamed: JP121.3, R203.1
unnamed: JP121.1, R204.2
unnamed: JP122.1, R202.1
unnamed: JP122.3, R201.2
unnamed: D41.A, JP123.1
unnamed: D41.C, R205.2
unnamed: JP124.3, R208.1
unnamed: JP124.1, R209.2
unnamed: JP125.1, R207.1
unnamed: JP125.3, R206.2
unnamed: D42.A, JP126.1
unnamed: D42.C, R210.2
unnamed: JP127.3, R213.1
unnamed: JP127.1, R214.2
unnamed: JP128.1, R212.1
unnamed: JP128.3, R211.2
unnamed: D43.A, JP129.1
unnamed: D43.C, R215.2
unnamed: JP130.3, R218.1
unnamed: JP130.1, R219.2
unnamed: JP131.1, R217.1
unnamed: JP131.3, R216.2
unnamed: D44.A, JP132.1
unnamed: D44.C, R220.2
unnamed: JP133.3, R223.1
unnamed: JP133.1, R224.2
unnamed: JP134.1, R222.1
unnamed: JP134.3, R221.2
unnamed: D45.A, JP135.1
unnamed: D45.C, R225.2
unnamed: JP136.3, R228.1
unnamed: JP136.1, R229.2
unnamed: JP137.1, R227.1
unnamed: JP137.3, R226.2
unnamed: D46.A, JP138.1
unnamed: D46.C, R230.2
unnamed: JP139.3, R233.1
unnamed: JP139.1, R234.2
unnamed: JP140.1, R232.1
unnamed: JP140.3, R231.2
unnamed: D47.A, JP141.1
unnamed: D47.C, R235.2
unnamed: JP142.3, R238.1
unnamed: JP142.1, R239.2
unnamed: JP143.1, R237.1
unnamed: JP143.3, R236.2
unnamed: D48.A, JP144.1
unnamed: D48.C, R240.2
unnamed: JP145.3, R243.1
unnamed: JP145.1, R244.2
unnamed: JP146.1, R242.1
unnamed: JP146.3, R241.2
unnamed: D49.A, JP147.1
unnamed: D49.C, R245.2
unnamed: JP148.3, R248.1
unnamed: JP148.1, R249.2
unnamed: JP149.1, R247.1
unnamed: JP149.3, R246.2
unnamed: D50.A, JP150.1
unnamed: D50.C, R250.2
unnamed: JP151.3, R253.1
unnamed: JP151.1, R254.2
unnamed: JP152.1, R252.1
unnamed: JP152.3, R251.2
unnamed: D51.A, JP153.1
unnamed: D51.C, R255.2
unnamed: JP154.3, R258.1
unnamed: JP154.1, R259.2
unnamed: JP155.1, R257.1
unnamed: JP155.3, R256.2
unnamed: D52.A, JP156.1
unnamed: D52.C, R260.2
unnamed: JP157.3, R263.1
unnamed: JP157.1, R264.2
unnamed: JP158.1, R262.1
unnamed: JP158.3, R261.2
unnamed: D53.A, JP159.1
unnamed: D53.C, R265.2
unnamed: JP160.3, R268.1
unnamed: JP160.1, R269.2
unnamed: JP161.1, R267.1
unnamed: JP161.3, R266.2
unnamed: D54.A, JP162.1
unnamed: D54.C, R270.2
unnamed: JP163.3, R273.1
unnamed: JP163.1, R274.2
unnamed: JP164.1, R272.1
unnamed: JP164.3, R271.2
unnamed: D55.A, JP165.1
unnamed: D55.C, R275.2
unnamed: JP166.3, R278.1
unnamed: JP166.1, R279.2
unnamed: JP167.1, R277.1
unnamed: JP167.3, R276.2
unnamed: D56.A, JP168.1
unnamed: D56.C, R280.2
unnamed: JP169.3, R283.1
unnamed: JP169.1, R284.2
unnamed: JP170.1, R282.1
unnamed: JP170.3, R281.2
unnamed: D57.A, JP171.1
unnamed: D57.C, R285.2
unnamed: JP172.3, R288.1
unnamed: JP172.1, R289.2
unnamed: JP173.1, R287.1
unnamed: JP173.3, R286.2
unnamed: D58.A, JP174.1
unnamed: D58.C, R290.2
unnamed: JP175.3, R293.1
unnamed: JP175.1, R294.2
unnamed: JP176.1, R292.1
unnamed: JP176.3, R291.2
unnamed: D59.A, JP177.1
unnamed: D59.C, R295.2
unnamed: JP178.3, R298.1
unnamed: JP178.1, R299.2
unnamed: JP179.1, R297.1
unnamed: JP179.3, R296.2
unnamed: D60.A, JP180.1
unnamed: D60.C, R300.2
unnamed: JP181.3, R303.1
unnamed: JP181.1, R304.2
unnamed: JP182.1, R302.1
unnamed: JP182.3, R301.2
unnamed: D61.A, JP183.1
unnamed: D61.C, R305.2
unnamed: JP184.3, R308.1
unnamed: JP184.1, R309.2
unnamed: JP185.1, R307.1
unnamed: JP185.3, R306.2
unnamed: D62.A, JP186.1
unnamed: D62.C, R310.2
unnamed: JP187.3, R313.1
unnamed: JP187.1, R314.2
unnamed: JP188.1, R312.1
unnamed: JP188.3, R311.2
unnamed: D63.A, JP189.1
unnamed: D63.C, R315.2
unnamed: JP190.3, R318.1
unnamed: JP190.1, R319.2
unnamed: JP191.1, R317.1
unnamed: JP191.3, R316.2
unnamed: D64.A, JP192.1
unnamed: D64.C, R320.2
SCK/SCL: J1.4, R2.2, TP4.1, U1.2
SCK/SCL1: J4.4, R7.2, TP8.1, U2.2
SCK/SCL2: J7.4, R12.2, TP12.1, U3.2
SCK/SCL3: J10.4, R17.2, TP16.1, U4.2
SCK/SCL4: J13.4, R22.2, TP20.1, U5.2
SCK/SCL5: J16.4, R27.2, TP24.1, U6.2
SCK/SCL6: J19.4, R32.2, TP28.1, U7.2
SCK/SCL7: J22.4, R37.2, TP32.1, U8.2
SCK/SCL8: J25.4, R42.2, TP36.1, U9.2
SCK/SCL9: J28.4, R47.2, TP40.1, U10.2
SCK/SCL10: J31.4, R52.2, TP44.1, U11.2
SCK/SCL11: J34.4, R57.2, TP48.1, U12.2
SCK/SCL12: J37.4, R62.2, TP52.1, U13.2
SCK/SCL13: J40.4, R67.2, TP56.1, U14.2
SCK/SCL14: J43.4, R72.2, TP60.1, U15.2
SCK/SCL15: J46.4, R77.2, TP64.1, U16.2
SCK/SCL16: J49.4, R82.2, TP68.1, U17.2
SCK/SCL17: J52.4, R87.2, TP72.1, U18.2
SCK/SCL18: J55.4, R92.2, TP76.1, U19.2
SCK/SCL19: J58.4, R97.2, TP80.1, U20.2
SCK/SCL20: J61.4, R102.2, TP84.1, U21.2
SCK/SCL21: J64.4, R107.2, TP88.1, U22.2
SCK/SCL22: J67.4, R112.2, TP92.1, U23.2
SCK/SCL23: J70.4, R117.2, TP96.1, U24.2
SCK/SCL24: J73.4, R122.2, TP100.1, U25.2
SCK/SCL25: J76.4, R127.2, TP104.1, U26.2
SCK/SCL26: J79.4, R132.2, TP108.1, U27.2
SCK/SCL27: J82.4, R137.2, TP112.1, U28.2
SCK/SCL28: J85.4, R142.2, TP116.1, U29.2
SCK/SCL29: J88.4, R147.2, TP120.1, U30.2
SCK/SCL30: J91.4, R152.2, TP124.1, U31.2
SCK/SCL31: J94.4, R157.2, TP128.1, U32.2
SCK/SCL32: J97.4, R162.2, TP132.1, U33.2
SCK/SCL33: J100.4, R167.2, TP136.1, U34.2
SCK/SCL34: J103.4, R172.2, TP140.1, U35.2
SCK/SCL35: J106.4, R177.2, TP144.1, U36.2
SCK/SCL36: J109.4, R182.2, TP148.1, U37.2
SCK/SCL37: J112.4, R187.2, TP152.1, U38.2
SCK/SCL38: J115.4, R192.2, TP156.1, U39.2
SCK/SCL39: J118.4, R197.2, TP160.1, U40.2
SCK/SCL40: J121.4, R202.2, TP164.1, U41.2
SCK/SCL41: J124.4, R207.2, TP168.1, U42.2
SCK/SCL42: J127.4, R212.2, TP172.1, U43.2
SCK/SCL43: J130.4, R217.2, TP176.1, U44.2
SCK/SCL44: J133.4, R222.2, TP180.1, U45.2
SCK/SCL45: J136.4, R227.2, TP184.1, U46.2
SCK/SCL46: J139.4, R232.2, TP188.1, U47.2
SCK/SCL47: J142.4, R237.2, TP192.1, U48.2
SCK/SCL48: J145.4, R242.2, TP196.1, U49.2
SCK/SCL49: J148.4, R247.2, TP200.1, U50.2
SCK/SCL50: J151.4, R252.2, TP204.1, U51.2
SCK/SCL51: J154.4, R257.2, TP208.1, U52.2
SCK/SCL52: J157.4, R262.2, TP212.1, U53.2
SCK/SCL53: J160.4, R267.2, TP216.1, U54.2
SCK/SCL54: J163.4, R272.2, TP220.1, U55.2
SCK/SCL55: J166.4, R277.2, TP224.1, U56.2
SCK/SCL56: J169.4, R282.2, TP228.1, U57.2
SCK/SCL57: J172.4, R287.2, TP232.1, U58.2
SCK/SCL58: J175.4, R292.2, TP236.1, U59.2
SCK/SCL59: J178.4, R297.2, TP240.1, U60.2
SCK/SCL60: J181.4, R302.2, TP244.1, U61.2
SCK/SCL61: J184.4, R307.2, TP248.1, U62.2
SCK/SCL62: J187.4, R312.2, TP252.1, U63.2
SCK/SCL63: J190.4, R317.2, TP256.1, U64.2
SDI/SDA: J1.3, R1.1, TP3.1, U1.4
SDI/SDA1: J4.3, R6.1, TP7.1, U2.4
SDI/SDA2: J7.3, R11.1, TP11.1, U3.4
SDI/SDA3: J10.3, R16.1, TP15.1, U4.4
SDI/SDA4: J13.3, R21.1, TP19.1, U5.4
SDI/SDA5: J16.3, R26.1, TP23.1, U6.4
SDI/SDA6: J19.3, R31.1, TP27.1, U7.4
SDI/SDA7: J22.3, R36.1, TP31.1, U8.4
SDI/SDA8: J25.3, R41.1, TP35.1, U9.4
SDI/SDA9: J28.3, R46.1, TP39.1, U10.4
SDI/SDA10: J31.3, R51.1, TP43.1, U11.4
SDI/SDA11: J34.3, R56.1, TP47.1, U12.4
SDI/SDA12: J37.3, R61.1, TP51.1, U13.4
SDI/SDA13: J40.3, R66.1, TP55.1, U14.4
SDI/SDA14: J43.3, R71.1, TP59.1, U15.4
SDI/SDA15: J46.3, R76.1, TP63.1, U16.4
SDI/SDA16: J49.3, R81.1, TP67.1, U17.4
SDI/SDA17: J52.3, R86.1, TP71.1, U18.4
SDI/SDA18: J55.3, R91.1, TP75.1, U19.4
SDI/SDA19: J58.3, R96.1, TP79.1, U20.4
SDI/SDA20: J61.3, R101.1, TP83.1, U21.4
SDI/SDA21: J64.3, R106.1, TP87.1, U22.4
SDI/SDA22: J67.3, R111.1, TP91.1, U23.4
SDI/SDA23: J70.3, R116.1, TP95.1, U24.4
SDI/SDA24: J73.3, R121.1, TP99.1, U25.4
SDI/SDA25: J76.3, R126.1, TP103.1, U26.4
SDI/SDA26: J79.3, R131.1, TP107.1, U27.4
SDI/SDA27: J82.3, R136.1, TP111.1, U28.4
SDI/SDA28: J85.3, R141.1, TP115.1, U29.4
SDI/SDA29: J88.3, R146.1, TP119.1, U30.4
SDI/SDA30: J91.3, R151.1, TP123.1, U31.4
SDI/SDA31: J94.3, R156.1, TP127.1, U32.4
SDI/SDA32: J97.3, R161.1, TP131.1, U33.4
SDI/SDA33: J100.3, R166.1, TP135.1, U34.4
SDI/SDA34: J103.3, R171.1, TP139.1, U35.4
SDI/SDA35: J106.3, R176.1, TP143.1, U36.4
SDI/SDA36: J109.3, R181.1, TP147.1, U37.4
SDI/SDA37: J112.3, R186.1, TP151.1, U38.4
SDI/SDA38: J115.3, R191.1, TP155.1, U39.4
SDI/SDA39: J118.3, R196.1, TP159.1, U40.4
SDI/SDA40: J121.3, R201.1, TP163.1, U41.4
SDI/SDA41: J124.3, R206.1, TP167.1, U42.4
SDI/SDA42: J127.3, R211.1, TP171.1, U43.4
SDI/SDA43: J130.3, R216.1, TP175.1, U44.4
SDI/SDA44: J133.3, R221.1, TP179.1, U45.4
SDI/SDA45: J136.3, R226.1, TP183.1, U46.4
SDI/SDA46: J139.3, R231.1, TP187.1, U47.4
SDI/SDA47: J142.3, R236.1, TP191.1, U48.4
SDI/SDA48: J145.3, R241.1, TP195.1, U49.4
SDI/SDA49: J148.3, R246.1, TP199.1, U50.4
SDI/SDA50: J151.3, R251.1, TP203.1, U51.4
SDI/SDA51: J154.3, R256.1, TP207.1, U52.4
SDI/SDA52: J157.3, R261.1, TP211.1, U53.4
SDI/SDA53: J160.3, R266.1, TP215.1, U54.4
SDI/SDA54: J163.3, R271.1, TP219.1, U55.4
SDI/SDA55: J166.3, R276.1, TP223.1, U56.4
SDI/SDA56: J169.3, R281.1, TP227.1, U57.4
SDI/SDA57: J172.3, R286.1, TP231.1, U58.4
SDI/SDA58: J175.3, R291.1, TP235.1, U59.4
SDI/SDA59: J178.3, R296.1, TP239.1, U60.4
SDI/SDA60: J181.3, R301.1, TP243.1, U61.4
SDI/SDA61: J184.3, R306.1, TP247.1, U62.4
SDI/SDA62: J187.3, R311.1, TP251.1, U63.4
SDI/SDA63: J190.3, R316.1, TP255.1, U64.4
SDO/ADR: JP1.2, U1.5
SDO/ADR1: JP4.2, U2.5
SDO/ADR2: JP7.2, U3.5
SDO/ADR3: JP10.2, U4.5
SDO/ADR4: JP13.2, U5.5
SDO/ADR5: JP16.2, U6.5
SDO/ADR6: JP19.2, U7.5
SDO/ADR7: JP22.2, U8.5
SDO/ADR8: JP25.2, U9.5
SDO/ADR9: JP28.2, U10.5
SDO/ADR10: JP31.2, U11.5
SDO/ADR11: JP34.2, U12.5
SDO/ADR12: JP37.2, U13.5
SDO/ADR13: JP40.2, U14.5
SDO/ADR14: JP43.2, U15.5
SDO/ADR15: JP46.2, U16.5
SDO/ADR16: JP49.2, U17.5
SDO/ADR17: JP52.2, U18.5
SDO/ADR18: JP55.2, U19.5
SDO/ADR19: JP58.2, U20.5
SDO/ADR20: JP61.2, U21.5
SDO/ADR21: JP64.2, U22.5
SDO/ADR22: JP67.2, U23.5
SDO/ADR23: JP70.2, U24.5
SDO/ADR24: JP73.2, U25.5
SDO/ADR25: JP76.2, U26.5
SDO/ADR26: JP79.2, U27.5
SDO/ADR27: JP82.2, U28.5
SDO/ADR28: JP85.2, U29.5
SDO/ADR29: JP88.2, U30.5
SDO/ADR30: JP91.2, U31.5
SDO/ADR31: JP94.2, U32.5
SDO/ADR32: JP97.2, U33.5
SDO/ADR33: JP100.2, U34.5
SDO/ADR34: JP103.2, U35.5
SDO/ADR35: JP106.2, U36.5
SDO/ADR36: JP109.2, U37.5
SDO/ADR37: JP112.2, U38.5
SDO/ADR38: JP115.2, U39.5
SDO/ADR39: JP118.2, U40.5
SDO/ADR40: JP121.2, U41.5
SDO/ADR41: JP124.2, U42.5
SDO/ADR42: JP127.2, U43.5
SDO/ADR43: JP130.2, U44.5
SDO/ADR44: JP133.2, U45.5
SDO/ADR45: JP136.2, U46.5
SDO/ADR46: JP139.2, U47.5
SDO/ADR47: JP142.2, U48.5
SDO/ADR48: JP145.2, U49.5
SDO/ADR49: JP148.2, U50.5
SDO/ADR50: JP151.2, U51.5
SDO/ADR51: JP154.2, U52.5
SDO/ADR52: JP157.2, U53.5
SDO/ADR53: JP160.2, U54.5
SDO/ADR54: JP163.2, U55.5
SDO/ADR55: JP166.2, U56.5
SDO/ADR56: JP169.2, U57.5
SDO/ADR57: JP172.2, U58.5
SDO/ADR58: JP175.2, U59.5
SDO/ADR59: JP178.2, U60.5
SDO/ADR60: JP181.2, U61.5
SDO/ADR61: JP184.2, U62.5
SDO/ADR62: JP187.2, U63.5
SDO/ADR63: JP190.2, U64.5
VDD: C1.1, J1.2, JP2.2, JP3.2, R3.2, TP2.1, U1.1, U1.6, U1.10
VDD1: C2.1, J4.2, JP5.2, JP6.2, R8.2, TP6.1, U2.1, U2.6, U2.10
VDD2: C3.1, J7.2, JP8.2, JP9.2, R13.2, TP10.1, U3.1, U3.6, U3.10
VDD3: C4.1, J10.2, JP11.2, JP12.2, R18.2, TP14.1, U4.1, U4.6, U4.10
VDD4: C5.1, J13.2, JP14.2, JP15.2, R23.2, TP18.1, U5.1, U5.6, U5.10
VDD5: C6.1, J16.2, JP17.2, JP18.2, R28.2, TP22.1, U6.1, U6.6, U6.10
VDD6: C7.1, J19.2, JP20.2, JP21.2, R33.2, TP26.1, U7.1, U7.6, U7.10
VDD7: C8.1, J22.2, JP23.2, JP24.2, R38.2, TP30.1, U8.1, U8.6, U8.10
VDD8: C9.1, J25.2, JP26.2, JP27.2, R43.2, TP34.1, U9.1, U9.6, U9.10
VDD9: C10.1, J28.2, JP29.2, JP30.2, R48.2, TP38.1, U10.1, U10.6, U10.10
VDD10: C11.1, J31.2, JP32.2, JP33.2, R53.2, TP42.1, U11.1, U11.6, U11.10
VDD11: C12.1, J34.2, JP35.2, JP36.2, R58.2, TP46.1, U12.1, U12.6, U12.10
VDD12: C13.1, J37.2, JP38.2, JP39.2, R63.2, TP50.1, U13.1, U13.6, U13.10
VDD13: C14.1, J40.2, JP41.2, JP42.2, R68.2, TP54.1, U14.1, U14.6, U14.10
VDD14: C15.1, J43.2, JP44.2, JP45.2, R73.2, TP58.1, U15.1, U15.6, U15.10
VDD15: C16.1, J46.2, JP47.2, JP48.2, R78.2, TP62.1, U16.1, U16.6, U16.10
VDD16: C17.1, J49.2, JP50.2, JP51.2, R83.2, TP66.1, U17.1, U17.6, U17.10
VDD17: C18.1, J52.2, JP53.2, JP54.2, R88.2, TP70.1, U18.1, U18.6, U18.10
VDD18: C19.1, J55.2, JP56.2, JP57.2, R93.2, TP74.1, U19.1, U19.6, U19.10
VDD19: C20.1, J58.2, JP59.2, JP60.2, R98.2, TP78.1, U20.1, U20.6, U20.10
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
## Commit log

2022-06-02 Add .gitignore
2022-06-02 Add datasheet
2022-06-02 Add README
2022-06-02 Create BMP384 library file
2022-06-02 Add schematic and board files
2022-06-02 Add proto gerbers
2022-06-02 Add panel gerbers
2022-06-02 Remove proto gerbers
2022-07-21 Add Qwiic Micro files
2022-07-21 Update README.md
    Updating for Micro release.
2022-07-25 Update README
    Adding Qwiic Micro photo.
2023-03-28 Remove library file
    BMP384 is in SFE Eagle library, update part in design
